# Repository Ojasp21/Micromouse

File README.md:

# Micromouse
Design a micromouse PCB from scratch and implement maze floodfill algorithms on it!  

## Table of Contents

- [Micromouse](#micromouse)
  - [Table of Contents](#table-of-contents)
  - [About The Project](#about-the-project)
  - [Project Workflow](#project-workflow)
  - [Hardware Used](#hardware-used)
  - [Perfboard Testing](#perfboard-testing)
  - [PCB Model](#pcb-model)
  - [CAD Models](#cad-models)
    - [Features](#features)
  - [Floodfill Algorithm Simulation](#floodfill-algorithm-simulation)
  - [Software Used](#software-used)
  - [Future Work](#future-work)
  - [Contributors](#contributors)
  - [Resources](#resources)
  - [Acknowledgements](#acknowledgements)
  - [License](#license)

## About The Project
The aim of this project is to design and assemble a full size micromouse which will use floodfill and other path finding algorithms to solve a maze.    

The dimensions of our full-size micromouse is 11.5 x 10 cm

## Project Workflow  
#### Research
- Learning and understanding Embedded C by referring to the firmware used in [SRA WallE](https://github.com/SRA-VJTI/Wall-E) and [MazeBlaze](https://github.com/SurajSonawane2415/MazeBlaze)
- Understanding what Micromouse is and how maze solving algorithms like floodfill actually work
- Deciding the constraints for our micrmouse and selecting hardware and electronic componenets accordingly. We did a detailed review of existing micromouse designs and features and arrived at our present design.
#### CAD and PCB Design
- Designing a CAD Model on [Onshape.com](https://www.onshape.com/en/). We went through various iterations and design options. After weighing the pro's and cons of a 4 motor design, we settled for a 2 motor design with a suction fan in the centre.
- PCB Design keeping mechanical design in mind during routing. Once the pcb design and routing is finalised, the order for the PCB is placed.
#### Perfboard Testing and PID
- Testing our pcb schematic on a perfboard and recreating the final micromouse design on a perfboard.
- Implementing PID on the perfboard Micromouse to refine the code and understand the implementation of control systems.
#### PCB Soldering and Assembly
- Once the PCB is delivered, we will solder the components onto the PCB and assemble the bot with the 3D-printed mounts
- After this, the testing of the final Micromouse in a 6ft x 6ft maze will begin.

## Hardware Used

|     Components        |          Description          |
| --------------------- | ----------------------------- |
| [ESP32 WROOM-E](https://robu.in/product/espressif-esp32-wroom-32e-16m-128mbit-flash-wifi-bluetooth-module/)           | Microcontroller |
| [VL 5310X](https://robu.in/product/gy-53-vl53l0x-laser-tof-flight-time-ranging-sensor-module-serial-port-pwm-output/)  | ToF sensor4 |
| [DRV8833](https://robu.in/product/drv8833-2-channel-dc-motor-driver-module/) | Motor Driver |
| [N12 600 RPM With Encoders](https://robu.in/product/n12-2-4v-1200rpm-metal-gear-motor-with-encoder/) | Motors |
| [IR Sensors](https://robocraze.com/products/5mm-ir-transmitter-receiver-pair?variant=40192346980505&currency=INR&utm_medium=product_sync&utm_source=google&utm_content=sag_organic&utm_campaign=sag_organic&campaignid=21586511453&adgroupid=&keyword=&device=c&gad_source=1&gclid=Cj0KCQjw_sq2BhCUARIsAIVqmQtLaP4tnieC83a3KD7llLIWLyPyhrdU7XTjEk-4mGGGtPHHxCPh_YoaAsz_EALw_wcB) | Infrared Emitter-Receiver Pair |

## Perfboard Testing
|             |  |  |  |
:-------------------------:|:-------------------------:|:-------------------------:|:-------------------------:

## PCB Model
- View of the PCB Model front and back:       
  
|             |  |    
:-------------------------:|:-------------------------:|

- View of the PCB Routing - front and back:      
  
|             |  |  
:-------------------------:|:-------------------------:|

## CAD Models 
- First design iteration was a four motor design with a suction fan. However this design was not suitable for fitting an enitre Esp-Devkit. 

|             |  |  
:-------------------------:|:-------------------------:|

- Second and final design is a two-motor design with a suction fan. Certain drawbacks of the four-motor design was addressed in this design.  

### Features 
- Suction Fan to improve traction and potentially turn at faster speeds without flipping over.  
- Custom mount to hold the motors, shaft and suction fan in place and reduce the distance between the plate and the ground.
-  Gears to run 4 wheels on two motors  
  
|             |  |  |
:-------------------------:|:-------------------------:|:-------------------------:|
  
## Floodfill Algorithm Simulation
The path solving algorithm floodfill has been successfully implemented in the software simulation.  
[Floodfill simulation](https://github.com/Ojasp21/Micromouse/blob/main/assets/flood%20fill%20simulation.mov)

## Software Used 
- Mechanical Design - [Onshape](https://www.onshape.com/en/)
- PCB Design - [KiCad 8.0.4](https://www.kicad.org/)
- Embedded C and Firmware - [ESP-IDF](https://docs.espressif.com/projects/esp-idf/en/stable/esp32/get-started/index.html)

## Future Work
- [ ] Implementing the flood-fill algorithm on it
- [ ] Optimizing the bot to achieve high speeds and taking turns as diagonals

## Contributors
- [Ojas Patil](https://github.com/Ojasp21)
- [Varun Nigudkar](https://github.com/fluffysunfish)
- [Vishal Mutha ](https://github.com/Vishal-Mutha)

## Resources
- [UCLA Micromouse Playlist](https://www.youtube.com/playlist?list=PLAWsHzw_h0iiPIaGyXAr44G0XfHfyjOe7) 
- [Mushak Github Repository](https://github.com/gautam-dev-maker/mushak/tree/main)
- [Mackorone MMS Github Repository](https://github.com/mackorone/mms) to run and test the floodfill simulation.

## Acknowledgements 
- [SRA VJTI](https://sravjti.in/) Eklavya 2024
- Special thanks to our mentors [Atharva Atre](https://github.com/AtharvaAtre), [Suraj Sonawane](https://github.com/SurajSonawane2415), and all the seniors at SRA, VJTI for their constant support and guidance throughout the project.

## License
[MIT License](https://opensource.org/license/mit/)

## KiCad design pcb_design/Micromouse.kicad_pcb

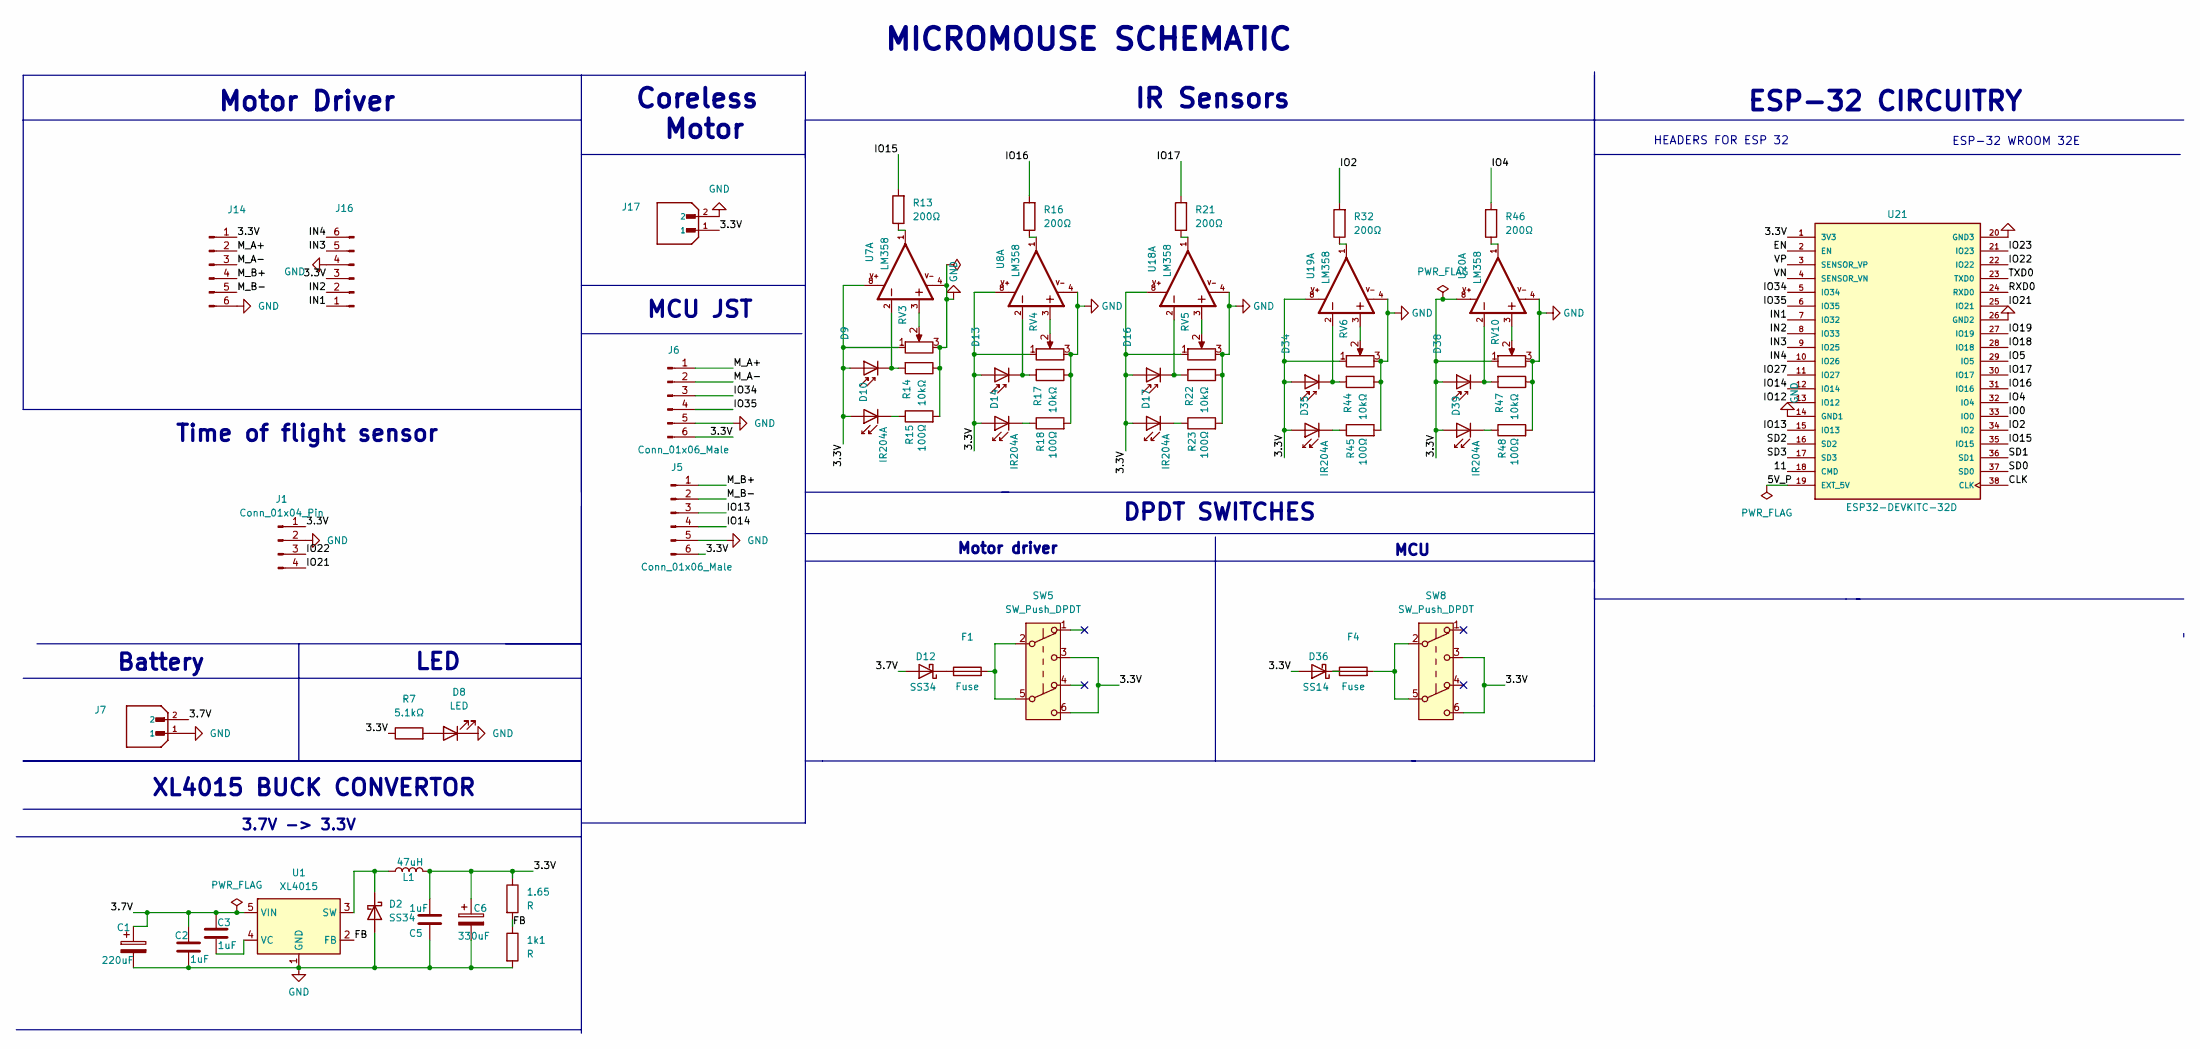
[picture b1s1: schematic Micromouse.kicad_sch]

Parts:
1.65, 1k1: R; R_0603_1608Metric
C1: 220uF; CP_Elec_6.3x7.7
C2, C3, C5: 1uF; C_0603_1608Metric
C6: 330uF; CP_Elec_8x10.5
D2: SS34; D_SMA
D8: LED; LED_0603_1608Metric
D9, D13, D16, D34, D38: D_Photo; LED2-2.54-D5.0MM
D10, D14, D17, D35, D39: IR204A; LED_D3.0mm_IRBlack
D12: SS34; D_SMB
D36: SS14; D_SMA
F1, F4: Fuse; SW_1-1571563-4
J1: Conn_01x04_Pin; PinHeader_1x04_P2.54mm_Vertical
J5, J6: Conn_01x06_Male; PinHeader_1x06_P2.54mm_Vertical
J7, J17: B2B-XH-A_LF__SN_; JST_B2B-XH-A_LF__SN_; PARTREV N/A
J14, J16: Conn_01x06_Pin; PinHeader_1x06_P2.54mm_Vertical
L1: 47uH; L_10.4x10.4_H4.8
R7: 5.1kΩ; R_0603_1608Metric
R13, R16, R21, R32, R46: 200Ω; R_0603_1608Metric
R14, R17, R22, R44, R47: 10kΩ; R_0603_1608Metric
R15, R18, R23, R45, R48: 100Ω; R_0603_1608Metric
RV3, RV4, RV5, RV6, RV10: R_Potentiometer; TRIM_3362P-1-253LF123
SW5, SW8: SW_Push_DPDT; SW_TL2230OAF140
U1: XL4015; TO-263-5_TabPin3
U7, U8, U18, U19, U20: LM358; SOIC8_150MIL
U21: ESP32-DEVKITC-32D; MODULE_ESP32-DEVKITC-32D; PARTREV 4

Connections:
/3.3V: 1.65.1, C5.1, C6.1, D9.2 (A), D10.2 (A), D13.2 (A), D14.2 (A), D16.2 (A), D17.2 (A), D34.2 (A), D35.2 (A), D36.2 (A), D38.2 (A), D39.2 (A), J1.1, J5.6, J6.6, J14.1, J16.3, J17.1, L1.2, R7.1, RV3.1, RV4.1, RV5.1, RV6.1, RV10.1, SW5.3 (C), SW5.6 (C), SW8.3 (C), SW8.6 (C), U7.8, U8.8, U18.8, U19.8, U20.8, U21.1 (3V3)
/3.7V: C1.1, C2.1, C3.1, D12.2 (A), J7.2, U1.5 (VIN)
/5V_P: U21.19 (EXT_5V)
/11: U21.18 (CMD)
/CLK: U21.38 (CLK)
/EN: U21.2 (EN)
/FB: 1.65.2, 1k1.1, U1.2 (FB)
/IN1: J16.1, U21.7 (IO32)
/IN2: J16.2, U21.8 (IO33)
/IN3: J16.5, U21.9 (IO25)
/IN4: J16.6, U21.10 (IO26)
/IO0: U21.33 (IO0)
/IO2: R32.2, U21.34 (IO2)
/IO4: R46.2, U21.32 (IO4)
/IO5: U21.29 (IO5)
/IO12: U21.13 (IO12)
/IO13: J5.3, U21.15 (IO13)
/IO14: J5.4, U21.12 (IO14)
/IO15: R13.2, U21.35 (IO15)
/IO16: R16.2, U21.31 (IO16)
/IO17: R21.2, U21.30 (IO17)
/IO18: U21.28 (IO18)
/IO19: U21.27 (IO19)
/IO21: J1.4, U21.25 (IO21)
/IO22: J1.3, U21.22 (IO22)
/IO23: U21.21 (IO23)
/IO27: U21.11 (IO27)
/IO34: J6.3, U21.5 (IO34)
/IO35: J6.4, U21.6 (IO35)
/M_A+: J6.1, J14.2
/M_A-: J6.2, J14.3
/M_B+: J5.1, J14.4
/M_B-: J5.2, J14.5
/RXD0: U21.24 (RXD0)
/SD0: U21.37 (SD0)
/SD1: U21.36 (SD1)
/SD2: U21.16 (SD2)
/SD3: U21.17 (SD3)
/TXD0: U21.23 (TXD0)
/VN: U21.4 (SENSOR_VN)
/VP: U21.3 (SENSOR_VP)
GND: 1k1.2, C1.2, C2.2, C5.2, C6.2, D2.2 (A), D8.1 (K), J1.2, J5.5, J6.5, J7.1, J14.6, J16.4, J17.2, R14.1, R15.2, R17.1, R18.2, R22.1, R23.2, R44.1, R45.2, R47.1, R48.2, RV3.3, RV4.3, RV5.3, RV6.3, RV10.3, U1.1 (GND), U7.4, U8.4, U18.4, U19.4, U20.4, U21.14 (GND1), U21.20 (GND3), U21.26 (GND2)
unnamed: D2.1 (K), L1.1, U1.3 (SW)
unnamed: D8.2 (A), R7.2
unnamed: D9.1 (K), R14.2, U7.2
unnamed: D10.1 (K), R15.1
unnamed: D12.1 (K), F1.1
unnamed: D13.1 (K), R17.2, U8.2
unnamed: D14.1 (K), R18.1
unnamed: D16.1 (K), R22.2, U18.2
unnamed: D17.1 (K), R23.1
unnamed: D34.1 (K), R44.2, U19.2
unnamed: D35.1 (K), R45.1
unnamed: D36.1 (K), F4.1
unnamed: D38.1 (K), R47.2, U20.2
unnamed: D39.1 (K), R48.1
unnamed: F1.2, SW5.2 (B), SW5.5 (B)
unnamed: F4.2, SW8.2 (B), SW8.5 (B)
unnamed: R13.1, U7.1
unnamed: R16.1, U8.1
unnamed: R21.1, U18.1
unnamed: R32.1, U19.1
unnamed: R46.1, U20.1
unnamed: RV3.2, U7.3
unnamed: RV4.2, U8.3
unnamed: RV5.2, U18.3
unnamed: RV6.2, U19.3
unnamed: RV10.2, U20.3
unnamed: C3.2, U1.4 (VC)

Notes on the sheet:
Coreless Motor
MICROMOUSE SCHEMATIC
ESP-32 WROOM 32E
Battery
ESP-32 CIRCUITRY
DPDT SWITCHES
IR Sensors
MCU JST
3.7V -> 3.3V
HEADERS FOR ESP 32
MCU
XL4015 BUCK CONVERTOR
Motor driver
LED
Time of flight sensor
Motor Driver

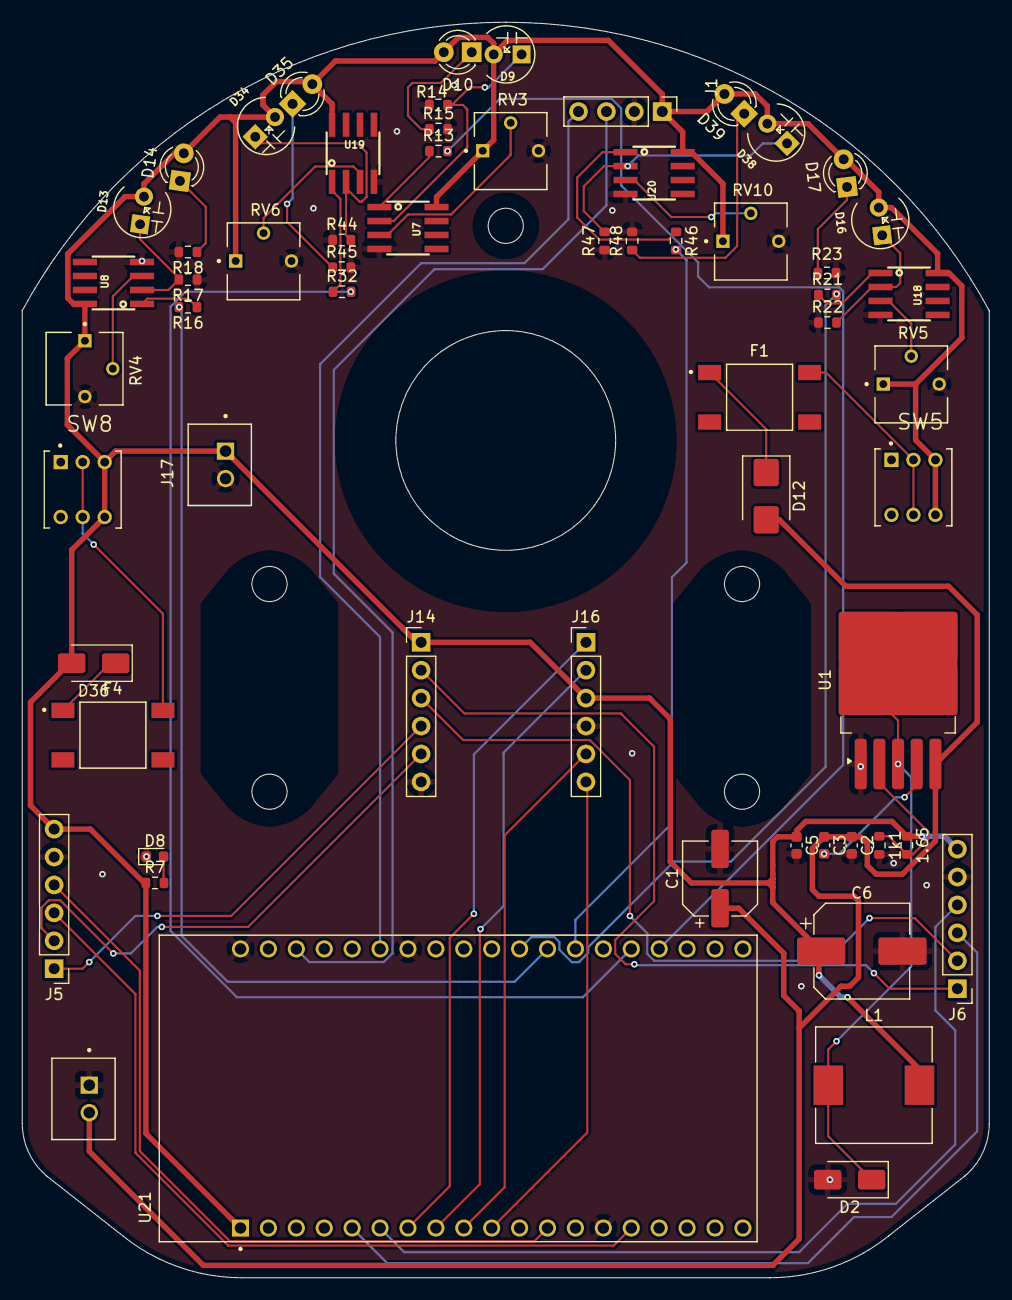
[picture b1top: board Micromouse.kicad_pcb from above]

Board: 2 copper layers, 88.0 x 114.3 mm, 61 parts (0 on the bottom side), 50 nets.

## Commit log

2024-08-11 Create cad_design
2024-08-29 assets for ReadMe
2024-08-31 Create assests
